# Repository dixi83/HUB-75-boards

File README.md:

# HUB-75 boards

The HUB-75 boards is a collection of break-out boards (BOBs) for HUB-75 connnectors found on re-purposed FPGA cards such as the 5A-75B and 5A-75E. These cards can be picked up for 10\~20 dollars from China and form an ideal basis for tinkering with FPGAs. Based on these cheap FPGA's a project has been spraked, called Litex-CNC, which aims to repurpose these cards to a cheap CNC controller. CNC-machines normally have field power which is 12\~24V and thus the FPGA cannot direclty be connected to the components of the machine. Therefore a set of break-out boards have been developed for GPIO inputs/outputs, stepgen, encoders, etc.

## Design philosophy
> Why not a hat one might ask? This project offers more flexibility. By combining different break-out can be combined to suit the machine that is being built. A hat also comes with a larger risk in design errors; smaller boards are easier to design, produce and check.

All BOBs will have the same dimensions of 85 mm x 56 mm. This size is equal to that of the Raspberry Pi 4, however the mounting holes are placed on the four corners and thus different from the RPi. Getting the mounting holes at the same location as the RPi made the design much more difficult. Placement of the connectors also hampers stacking these boards on top of each other, so not being to able to stack them on top of a RPi seems permissible.

The outputs of the BOBs will be on the bottom edge (long side). Field power and logic power are provided from the left side of the board. The HUB-75 connectors will be placed on the top of the boards. This makes it easier to route the digital signals and high-power signals separately from each other in the cabinet.

The smalles trace and spacing is 0.2 mm. These boards are designed to be ordered from an online PCB manufacturer. Some desktop milling machines might have the accuracy to create these traces, so you might give it a try when you are feeling lucky. The smallest holes (vias) are 0.3 mm in size.

All components are selected to be hand-solderable. This means that the following minimum sizes SMD components will be used:
- resistors, LED's, capacitors: SMD-1206
- diodes: SOD-123
- FET, transistors: SOT-23

## HUB-75 pinout
Each connector has 6 individual pins (1, 2, 3, 5, 6, and 7) and 8 shared pins (8 through 15). The standard pin-out of a HUB-75 connector is shown below.

| HUB75 pin | Pin   | Pin   | HUB75 pin |
|-----------|-------|-------|-----------|
| R0        | 1     | 2     | G0        |
| B0        | 3     | 4     | *GND*     |
| R1        | 5     | 6     | G1        |
| B1        | 7     | 8     | E         |
| A         | 9     | 10    | B         |
| C         | 11    | 12    | D         |
| CLK       | 13    | 14    | STB       |
| OE        | 15    | 16    | *GND*     |

Each HUB-75 connector will use the individual pins and in special cases one of the shared pins. In the design it should be taken into account that boards which uses the same shared pins might be mutual exclusive when the functions are different (different types of stepgen BOBs can off course be combined.

## Available BOBs
The table below shows the BOBs which are currently available in this repository, along with their status.

| Category  | Name                                                                        | Description                                                     | HUB-75    | Status              |
|-----------|-----------------------------------------------------------------------------|-----------------------------------------------------------------|-----------|---------------------|
| stepgen   | [HUB75-Differential_stepgen](HUB75-Differential_stepgen)                    | 3 differential stepgen channels, frequency up to 400 kHz        | 2 + 0.5   | Prototype-2 ordered |
| GPIO-out  | [HUB75-Sourcing_output](HUB75-Sourcing_output)                              | 12 channel sourcing output (<1 kHz, 4 A per channel, 4 A total) | 2         | Prototype-2 ordered |
| GPIO-in   | [HUB75-Sinking_input](HUB75-Sinking_input)                                  | 12 channel sinking input (< 1 kHz)                              | 2         | Untested            |
| GPIO-in   | [HUB75-Sinking_input_screw_terminals](HUB75-Sinking_input_screw_terminals)  | 6 channel sinking input with screw terminals (< 1 kHz)          | 2         | Untested            |

## Connecting the BOBs to your FPGA
On both the 5A-75B and the 5A-75E the `74HC245T` buffers are hard-wired as outputs. To be able to use the HUB-75 boards which require an input (as seen from the FPGA) some modifications on the board are required. Of both boards different versiosn exist, so the components can be at a different location on your board. Below are the locations of the buffer on a 5A-75B V6.1 (front) and 5A-75E V6.0 (back).

Each buffer has 8 channels, while every HUB-75 connector has 6 individual pins. When you replace a buffer you will cahnge the behavior of one HUB-75 connector and partly that of its neighbor. All HUB-75 boards assume that a connector is either fully configured as input or as output. Therefore it is recommended to change the buffers direclty adjacent to each other, so the minimum amount of available connectors (partly input/ouput) are wasted.

The following changes have to be made to the buffers:
* De-solder the `74HC245T` buffer, this buffer cannot be re-used because its pins are not 5 Volt tolerant when `Vcc` is 3.3 Volt.
* Cut the trace to the pin `Vcc` (pin 20) and wire it to a 3.3V source (for example the JTAG-header). If you don't do this, a buffer configure as input will put 5 Volts on the pins of the FPGA, which will definately fry that pin or the whole board.
* Cut the trace to the pin `DIR` (pin 1) and wire it to a GND source to configure the buffer as input.
* Replace the buffer with a buffer with 5V tolerant inputs, such as the `74LVC245` ([datasheet](https://www.ti.com/lit/ds/symlink/sn74lvc245a.pdf)).

After these modifications the board might look a like this (on this particular board a single buffer has been replace, as it is a test-board for LitexCNC).

TODO: picture to be taken

## License 
The boards in this repository are licensed unde Creative Commons BY-NC-SA. This means you are allowed to:
* **Share** — copy and redistribute the material in any medium or format
* **Adapt** — remix, transform, and build upon the material

As long as:
* **Attribution** — You must give appropriate credit, provide a link to the license, and indicate if changes were made. You may do so in any reasonable manner, but not in any way that suggests the licensor endorses you or your use.
* **NonCommercial** — You may not use the material for  commercial purposes. Of course you can use the machine you created or modified using these boards for commercial purposes. 
* **ShareAlike** — If you remix, transform, or build upon the material, you must distribute your contributions under the  same license  as the original.

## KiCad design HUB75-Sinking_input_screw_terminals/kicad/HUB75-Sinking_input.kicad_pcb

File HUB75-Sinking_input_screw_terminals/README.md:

# HUB-75 Sinking input screw terminals
Break-out board with 6 channel sinking input. The FPGA is galvanically separated from field power using opto-couplers.

## Features

- 1 HUB-75 output connector
- 6 channel sinking output using screw terminals
- 5\~24 V Field power with reverse polarity protection
- indicating LED for each output
- indicated switching frequency 1 kHz

## Applications

- PNP (souring) limit switches
- Momentary push-buttons
- Slow encoders, for example for user input

> **NOTE** <br> The `PC827` optocouplers have a maximum rated frequency of 80 kHz. It is recommended to start at a frequency of 1 kHz and work up from there.

## Example wiring

TODO: example

## Litex-CNC example configuration
Let's assume that the two HUB-745 connectors on this board are connected to J15 and J16 of the FPGA. To configure the pins for output, you can use the configuration-block below as a starting point. Optionaly the pin names can also be set in the configuration, making the HAL clearer.

``` json
{
    ...,
    "gpio_in": [
        {"pin": "j15:0"},
        {"pin": "j15:1"},
        {"pin": "j15:2"},
        {"pin": "j15:4"},
        {"pin": "j15:5"},
        {"pin": "j15:6"}
    ],
    ...
}
```

Alternatively, the BOB can also be used for PWM output. In that case the configuration may look something like below. In this example it is assumed that outputs on J16 are used for three encoders.

``` json
{
    ...,
    "encoders": [
        {  
            "pin_A":"j16:0",
            "pin_B":"j16:1"
        },
        {  
            "pin_A":"j16:2",
            "pin_B":"j16:4"
        },
        {  
            "pin_A":"j16:5",
            "pin_B":"j16:6"
        }
    ],
    ...
}
```

## Bill of materials

The table below gives the bill of materials used for this BOB and an indication of its price. The list is available as public list for the following companies:
* [Reichtelt](https://www.reichelt.de/my/1998173). This is non-affiliate link, I do not earn any money when you order this list from this specific vendor, nor the vendor endorses this project. Reichtelt is a supplyer for Western Europe.

When you order with Mouser or antohter supplier, please share a list here.

| Part. number          | Package   | Description                        | Datasheet | Amount | Price*  |
|-----------------------|-----------|------------------------------------|-----------|--------|---------|
| LTV827                | DIP-8     | Dual-channel opto-coupler          |           | 3      | € 0.31  |
| AO3401A               | SOT-23    | P-Channel MOSFET, 30V              |           | 1      | € 0.25  |
| ZENER 12V             | SOT-23    | 12V Zener diode***                 |           | 1      | € 0.05  |
| 4.7K                  | SMD 1206  | Resistor, 4.7 kOhm                 |           | 6      | € 0.03  |
| 10K                   | SMD 1206  | Resistor, 10 kOhm                  |           | 1      | € 0.03  |
| LED                   | SMD 1206  | LED, green, If > 20 mA             |           | 6      | € 0.08  |
| CAP 15N               | SMD 1206  | Capitor, 15 nF                     |           | 1      | € 0.02  |
| Phoenix_PT-1,5-3-5.0  | -         | JST XH conn. 2.5 mm pitch          |           | 6      | € 0.15  |
| Phoenix_PT-1,5-2-3.5  | -         | Screw/spring terminal 2.5 mm pitch |           | 2      | € 0.22  |
| BOX 2X8               | -         | Box header 2x8, 2.54 mm pitch      |           | 2      | € 0.16  |
| 2N7002**              | SOT-23    | N-Channel MOSFET (current mirror)  |           | 7      | € 0.04  |
| CL2N8-G**             | SOT-89    | LED-driver 20 mA (current mirror)  |           | 1      | € 0.39  |
| R**                   | SMD 1206  | Resistor, TBD Ohm (alternative)    |           | 6      | € 0.03  |

**NOTES**: 
1. The price is based on availability in the Netherlands with a single shop for all parts. Parts might be sourced cheaper depending on your location, available sources and the time you want to wait before receiving the components.
2. The components `CL2N8-G` and `2N7002` form a current mirror for driving the status LEDs. This current mirror can be replaced with a fixed resistor `R`, which should be calculated based on the voltage used for Field power.
3. The zener diode is only required when Field Power is >12 Volt for protecting the MOSFETs.

## Known issues

This board does not have any known issues yet.

If you find any issue, please file a bug using GitHub.

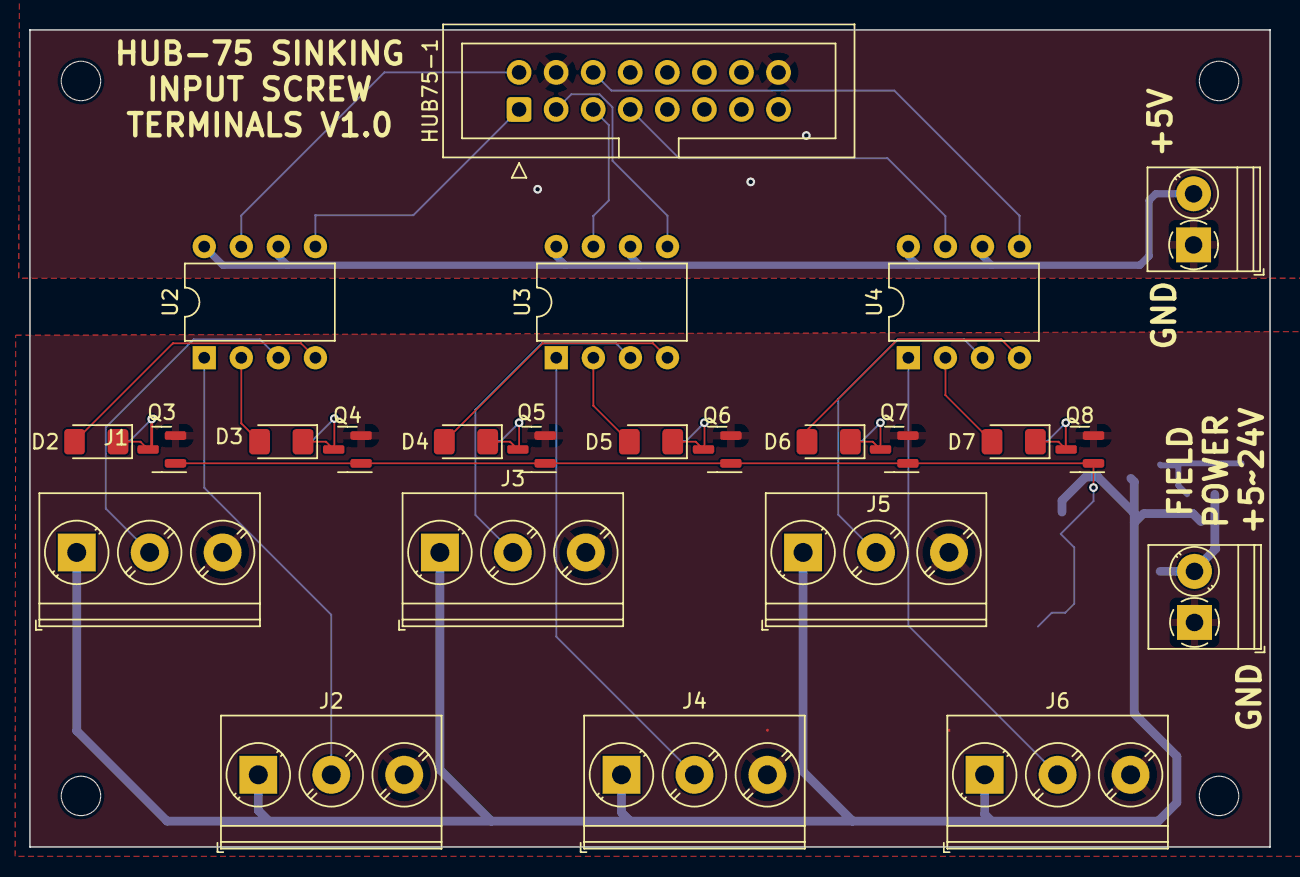
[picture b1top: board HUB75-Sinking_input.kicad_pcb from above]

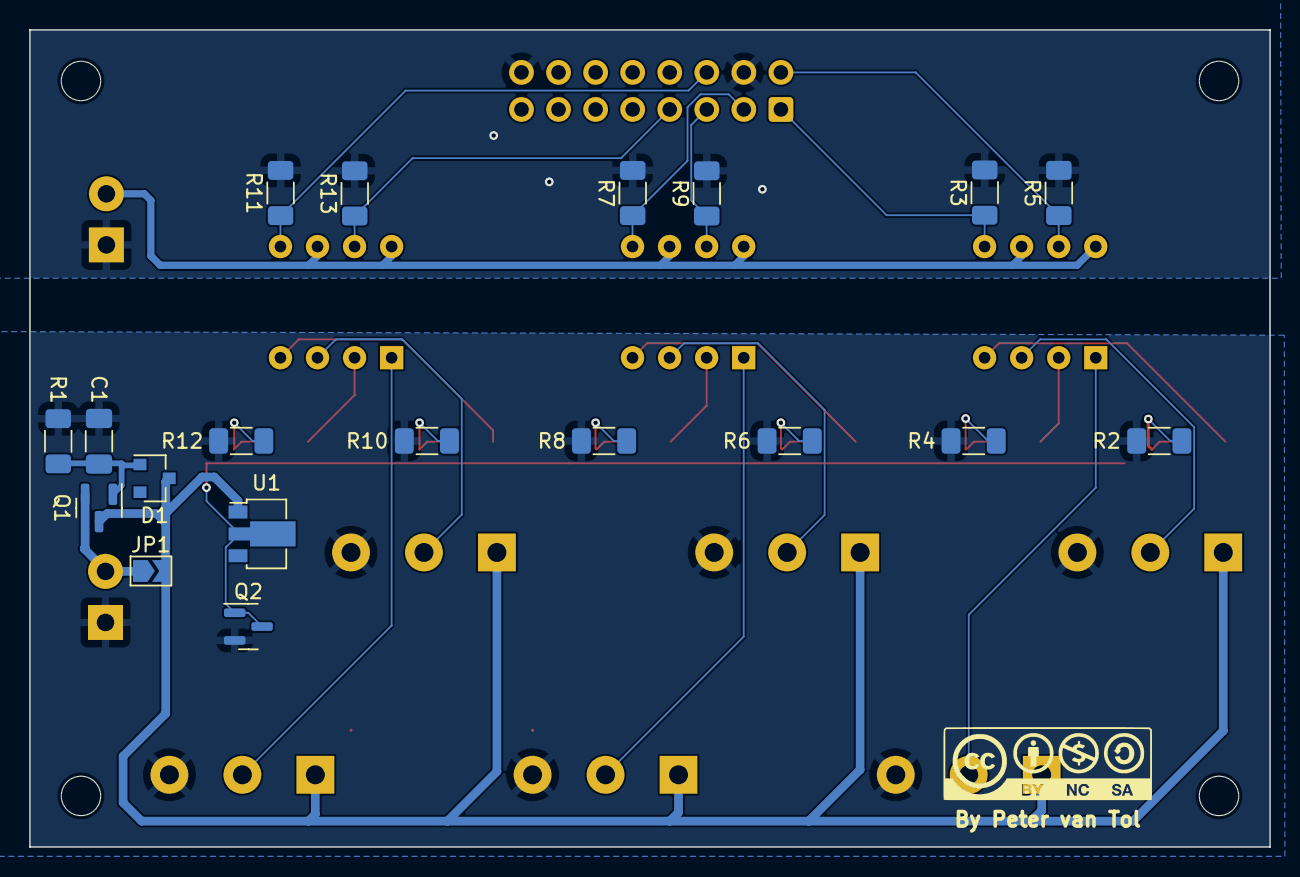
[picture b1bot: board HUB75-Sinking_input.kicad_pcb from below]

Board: 2 copper layers, 85.0 x 56.0 mm, 47 parts (19 on the bottom side), 31 nets.

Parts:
C1: 15nF; C_1206_3216Metric_Pad1.33x1.80mm_HandSolder
D1: D_Zener; D_SOT-23_ANK
D2, D3, D4, D5, D6, D7: LED_Small; LED_1206_3216Metric_Pad1.42x1.75mm_HandSolder
HOLE1, HOLE2, HOLE3, HOLE4: MountingHole_2.7mm_M2.5_DIN965
HUB75-1: Conn_02x08_Odd_Even; IDC-Header_2x08_P2.54mm_Vertical
J1, J2, J3, J4, J5: Conn_01x03_Male; TerminalBlock_Phoenix_PT-1,5-3-5.0-H_1x03_P5.00mm_Horizontal
J6: TerminalBlock_Phoenix:TerminalBlock_Phoenix_PT-1,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; TerminalBlock_Phoenix_PT-1,5-3-5.0-H_1x03_P5.00mm_Horizontal
JP1: Jumper_2_Open; SolderJumper-2_P1.3mm_Open_TrianglePad1.0x1.5mm
PWR1, PWR2: Screw_Terminal_01x02; TerminalBlock_Phoenix_PT-1,5-2-3.5-H_1x02_P3.50mm_Horizontal
Q1: AO3401A; SOT-23
Q2, Q3, Q4, Q5, Q6, Q7, Q8: 2N7002; SOT-23
R1: 10K; R_1206_3216Metric_Pad1.30x1.75mm_HandSolder
R2, R4, R6, R8, R10, R12: R; R_1206_3216Metric_Pad1.30x1.75mm_HandSolder
R3, R5, R7, R9, R11, R13: 4.7K; R_1206_3216Metric_Pad1.30x1.75mm_HandSolder
U1: CL2N8-G; SOT-89-3
U2, U3, U4: LTV-827; DIP-8_W7.62mm

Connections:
+5V: PWR2.2, U2.6, U2.8, U3.6, U3.8, U4.6, U4.8
CUR_MIRROR: Q2.1 (G), Q2.3 (D), Q3.1 (G), Q4.1 (G), Q5.1 (G), Q6.1 (G), Q7.1 (G), Q8.1 (G), U1.2 (GND)
GND: HUB75-1.4, HUB75-1.16, PWR2.1, R3.2, R5.2, R7.2, R9.2, R11.2, R13.2
GNDD: C1.2, J1.3, J2.3, J3.3, J4.3, J5.3, J6.3, PWR1.1, Q2.2 (S), Q3.2 (S), Q4.2 (S), Q5.2 (S), Q6.2 (S), Q7.2 (S), Q8.2 (S), R1.2, R2.1, R4.1, R6.1, R8.1, R10.1, R12.1
GPIO1-1: HUB75-1.1, R3.1, U2.5
GPIO1-2: HUB75-1.2, R5.1, U2.7
GPIO1-3: HUB75-1.3, R7.1, U3.5
GPIO1-4: HUB75-1.5, R9.1, U3.7
GPIO1-5: HUB75-1.6, R11.1, U4.5
GPIO1-6: HUB75-1.7, R13.1, U4.7
unnamed: C1.1, D1.2 (A), Q1.1 (G), R1.1
unnamed: D2.1 (K), Q3.3 (D), R2.2
unnamed: D2.2 (A), U2.4
unnamed: D3.1 (K), Q4.3 (D), R4.2
unnamed: D3.2 (A), U2.2
unnamed: D4.1 (K), Q5.3 (D), R6.2
unnamed: D4.2 (A), U3.4
unnamed: D5.1 (K), Q6.3 (D), R8.2
unnamed: D5.2 (A), U3.2
unnamed: D6.1 (K), Q7.3 (D), R10.2
unnamed: D6.2 (A), U4.4
unnamed: D7.1 (K), Q8.3 (D), R12.2
unnamed: D7.2 (A), U4.2
unnamed: J1.2, U2.3
unnamed: J2.2, U2.1
unnamed: J3.2, U3.3
unnamed: J4.2, U3.1
unnamed: J5.2, U4.3
unnamed: J6.2, U4.1
unnamed: JP1.1 (A), PWR1.2, Q1.2 (S)
VDD: D1.1 (K), J1.1, J2.1, J3.1, J4.1, J5.1, J6.1, JP1.2 (B), Q1.3 (D), U1.1 (VDD)

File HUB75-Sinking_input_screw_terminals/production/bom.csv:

"Source:","C:\Users\Martijn Diks\OneDrive\Documenten\documents\Projects\RatRig Killerbee\ControllerBoard\BOBs\HUB-75-boards-main\HUB75-Sinking_input_screw_terminals\kicad\HUB75-Sinking_input.kicad_sch"
"Date:","11-4-2023 18:23:18"
"Tool:","Eeschema (6.0.9)"
"Generator:","C:\Program Files\KiCad\6.0\bin\scripting\plugins/bom_csv_grouped_by_value.py"
"Component Count:","43"

"Individual Components:"

"Item","Qty","Reference(s)","Value","LibPart","Footprint","Datasheet"
"","","C1","15nF","Device:C","Capacitor_SMD:C_1206_3216Metric_Pad1.33x1.80mm_HandSolder","~"
"","","D1","D_Zener","Device:D_Zener","Diode_SMD:D_SOT-23_ANK","~"
"","","D2","LED_Small","Device:LED_Small","LED_SMD:LED_1206_3216Metric_Pad1.42x1.75mm_HandSolder","~"
"","","D3","LED_Small","Device:LED_Small","LED_SMD:LED_1206_3216Metric_Pad1.42x1.75mm_HandSolder","~"
"","","D4","LED_Small","Device:LED_Small","LED_SMD:LED_1206_3216Metric_Pad1.42x1.75mm_HandSolder","~"
"","","D5","LED_Small","Device:LED_Small","LED_SMD:LED_1206_3216Metric_Pad1.42x1.75mm_HandSolder","~"
"","","D6","LED_Small","Device:LED_Small","LED_SMD:LED_1206_3216Metric_Pad1.42x1.75mm_HandSolder","~"
"","","D7","LED_Small","Device:LED_Small","LED_SMD:LED_1206_3216Metric_Pad1.42x1.75mm_HandSolder","~"
"","","HUB75-1","Conn_02x08_Odd_Even","Connector_Generic:Conn_02x08_Odd_Even","Connector_IDC:IDC-Header_2x08_P2.54mm_Vertical","~"
"","","J1","Conn_01x03_Male","Connector:Conn_01x03_Male","Connector_JST:JST_XH_B3B-XH-A_1x03_P2.50mm_Vertical","~"
"","","J2","Conn_01x03_Male","Connector:Conn_01x03_Male","Connector_JST:JST_XH_B3B-XH-A_1x03_P2.50mm_Vertical","~"
"","","J3","Conn_01x03_Male","Connector:Conn_01x03_Male","Connector_JST:JST_XH_B3B-XH-A_1x03_P2.50mm_Vertical","~"
"","","J4","Conn_01x03_Male","Connector:Conn_01x03_Male","Connector_JST:JST_XH_B3B-XH-A_1x03_P2.50mm_Vertical","~"
"","","J5","Conn_01x03_Male","Connector:Conn_01x03_Male","Connector_JST:JST_XH_B3B-XH-A_1x03_P2.50mm_Vertical","~"
"","","J6","Conn_01x03_Male","Connector:Conn_01x03_Male","Connector_JST:JST_XH_B3B-XH-A_1x03_P2.50mm_Vertical","~"
"","","JP1","Jumper_2_Open","Jumper:Jumper_2_Open","Jumper:SolderJumper-2_P1.3mm_Open_TrianglePad1.0x1.5mm","~"
"","","PWR1","Screw_Terminal_01x02","Connector:Screw_Terminal_01x02","TerminalBlock_Phoenix:TerminalBlock_Phoenix_PT-1,5-2-3.5-H_1x02_P3.50mm_Horizontal","~"
"","","PWR2","Screw_Terminal_01x02","Connector:Screw_Terminal_01x02","TerminalBlock_Phoenix:TerminalBlock_Phoenix_PT-1,5-2-3.5-H_1x02_P3.50mm_Horizontal","~"
"","","Q1","AO3401A","Transistor_FET:AO3401A","Package_TO_SOT_SMD:SOT-23","http://www.aosmd.com/pdfs/datasheet/AO3401A.pdf"
"","","Q2","2N7002","Transistor_FET:2N7002","Package_TO_SOT_SMD:SOT-23","https://www.onsemi.com/pub/Collateral/NDS7002A-D.PDF"
"","","Q3","2N7002","Transistor_FET:2N7002","Package_TO_SOT_SMD:SOT-23","https://www.onsemi.com/pub/Collateral/NDS7002A-D.PDF"
"","","Q4","2N7002","Transistor_FET:2N7002","Package_TO_SOT_SMD:SOT-23","https://www.onsemi.com/pub/Collateral/NDS7002A-D.PDF"
"","","Q5","2N7002","Transistor_FET:2N7002","Package_TO_SOT_SMD:SOT-23","https://www.onsemi.com/pub/Collateral/NDS7002A-D.PDF"
"","","Q6","2N7002","Transistor_FET:2N7002","Package_TO_SOT_SMD:SOT-23","https://www.onsemi.com/pub/Collateral/NDS7002A-D.PDF"
"","","Q7","2N7002","Transistor_FET:2N7002","Package_TO_SOT_SMD:SOT-23","https://www.onsemi.com/pub/Collateral/NDS7002A-D.PDF"
"","","Q8","2N7002","Transistor_FET:2N7002","Package_TO_SOT_SMD:SOT-23","https://www.onsemi.com/pub/Collateral/NDS7002A-D.PDF"
"","","R1","10K","Device:R","Resistor_SMD:R_1206_3216Metric_Pad1.30x1.75mm_HandSolder","~"
"","","R2","R","Device:R","Resistor_SMD:R_1206_3216Metric_Pad1.30x1.75mm_HandSolder","~"
"","","R3","4.7K","Device:R","Resistor_SMD:R_1206_3216Metric_Pad1.30x1.75mm_HandSolder","~"
"","","R4","R","Device:R","Resistor_SMD:R_1206_3216Metric_Pad1.30x1.75mm_HandSolder","~"
"","","R5","4.7K","Device:R","Resistor_SMD:R_1206_3216Metric_Pad1.30x1.75mm_HandSolder","~"
"","","R6","R","Device:R","Resistor_SMD:R_1206_3216Metric_Pad1.30x1.75mm_HandSolder","~"
"","","R7","4.7K","Device:R","Resistor_SMD:R_1206_3216Metric_Pad1.30x1.75mm_HandSolder","~"
"","","R8","R","Device:R","Resistor_SMD:R_1206_3216Metric_Pad1.30x1.75mm_HandSolder","~"
"","","R9","4.7K","Device:R","Resistor_SMD:R_1206_3216Metric_Pad1.30x1.75mm_HandSolder","~"
"","","R10","R","Device:R","Resistor_SMD:R_1206_3216Metric_Pad1.30x1.75mm_HandSolder","~"
"","","R11","4.7K","Device:R","Resistor_SMD:R_1206_3216Metric_Pad1.30x1.75mm_HandSolder","~"
"","","R12","R","Device:R","Resistor_SMD:R_1206_3216Metric_Pad1.30x1.75mm_HandSolder","~"
"","","R13","4.7K","Device:R","Resistor_SMD:R_1206_3216Metric_Pad1.30x1.75mm_HandSolder","~"
"","","U1","CL2N8-G","Driver_LED:HV9921N8-G","Package_TO_SOT_SMD:SOT-89-3","https://cdn-reichelt.de/documents/datenblatt/A200/CL2_DS.pdf"
"","","U2","LTV-827","Isolator:LTV-827","Package_DIP:DIP-8_W7.62mm","http://optoelectronics.liteon.com/upload/download/DS-70-96-0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"
"","","U3","LTV-827","Isolator:LTV-827","Package_DIP:DIP-8_W7.62mm","http://optoelectronics.liteon.com/upload/download/DS-70-96-0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"
"","","U4","LTV-827","Isolator:LTV-827","Package_DIP:DIP-8_W7.62mm","http://optoelectronics.liteon.com/upload/download/DS-70-96-0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"



"Collated Components:"

"Item","Qty","Reference(s)","Value","LibPart","Footprint","Datasheet"
"1","1","C1","15nF","Device:C","Capacitor_SMD:C_1206_3216Metric_Pad1.33x1.80mm_HandSolder","~"
"2","1","D1","D_Zener","Device:D_Zener","Diode_SMD:D_SOT-23_ANK","~"
"3","6","D2, D3, D4, D5, D6, D7","LED_Small","Device:LED_Small","LED_SMD:LED_1206_3216Metric_Pad1.42x1.75mm_HandSolder","~"
"4","1","HUB75-1","Conn_02x08_Odd_Even","Connector_Generic:Conn_02x08_Odd_Even","Connector_IDC:IDC-Header_2x08_P2.54mm_Vertical","~"
"5","6","J1, J2, J3, J4, J5, J6","Conn_01x03_Male","Connector:Conn_01x03_Male","Connector_JST:JST_XH_B3B-XH-A_1x03_P2.50mm_Vertical","~"
"6","1","JP1","Jumper_2_Open","Jumper:Jumper_2_Open","Jumper:SolderJumper-2_P1.3mm_Open_TrianglePad1.0x1.5mm","~"
"7","2","PWR1, PWR2","Screw_Terminal_01x02","Connector:Screw_Terminal_01x02","TerminalBlock_Phoenix:TerminalBlock_Phoenix_PT-1,5-2-3.5-H_1x02_P3.50mm_Horizontal","~"
"8","1","Q1","AO3401A","Transistor_FET:AO3401A","Package_TO_SOT_SMD:SOT-23","http://www.aosmd.com/pdfs/datasheet/AO3401A.pdf"
"9","7","Q2, Q3, Q4, Q5, Q6, Q7, Q8","2N7002","Transistor_FET:2N7002","Package_TO_SOT_SMD:SOT-23","https://www.onsemi.com/pub/Collateral/NDS7002A-D.PDF"
"10","1","R1","10K","Device:R","Resistor_SMD:R_1206_3216Metric_Pad1.30x1.75mm_HandSolder","~"
"11","6","R2, R4, R6, R8, R10, R12","R","Device:R","Resistor_SMD:R_1206_3216Metric_Pad1.30x1.75mm_HandSolder","~"
"12","6","R3, R5, R7, R9, R11, R13","4.7K","Device:R","Resistor_SMD:R_1206_3216Metric_Pad1.30x1.75mm_HandSolder","~"
"13","1","U1","CL2N8-G","Driver_LED:HV9921N8-G","Package_TO_SOT_SMD:SOT-89-3","https://cdn-reichelt.de/documents/datenblatt/A200/CL2_DS.pdf"
"14","3","U2, U3, U4","LTV-827","Isolator:LTV-827","Package_DIP:DIP-8_W7.62mm","http://optoelectronics.liteon.com/upload/download/DS-70-96-0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"

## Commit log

2023-04-11 Added screw terminal BOB
2023-04-11 add Input board with screw terminals
2023-04-11 add images
2023-04-11 after the last edits
2023-04-14 DIR pin is 1

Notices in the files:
README.md:
CC BY-NC-SA 4.0
